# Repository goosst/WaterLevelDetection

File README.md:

# WaterLevelDetection

- [WaterLevelDetection](#waterleveldetection)
  * [Goal](#goal)
  * [Wishlist](#wishlist)
  * [Concept and used components](#concept-and-used-components)
    + [Controller](#controller)
    + [Pressure sensing and power electronics](#pressure-sensing-and-power-electronics)
  * [Implementation](#implementation)
    + [List of components](#list-of-components)
    + [Power electronics](#power-electronics)
    + [Current measurement](#current-measurement)
  * [Calibration](#calibration)
  * [Pictures](#pictures)
  * [Home assistant integration](#home-assistant-integration)
  * [(Possible) next steps](#-possible--next-steps)

## Goal

Measure the level of available water in a rainwater well and report in a home automation tool (here home assitant).

Spoiler alert: a 4-20mA, 24V converter using an ESP8266 was created for this.

## Wishlist

- Report level of water depth over WiFi (mqtt messages) 
- Since waterlevel only needs to be measured every x hours or days, use a deepsleep method to safe power and prevent heating / wear of components
- Use common components (through hole components for electronics, no SMD, ... )
- Be able to update software over the air

## Concept and used components

The measuring principle is based on water pressure, the pressure at the bottom of the well is proportional with the height of the water. Other methods using distance sensors sound quite unreliable (reflections, need to have a wide cone of free air to measure to the bottom of the well, ... ) or cumbersome (capacitive sensing).

### Controller
To take care of the Wifi and mqtt messages, an ESP8266 ([Wemos D1 mini](https://www.banggood.com/Geekcreit-D1-mini-V2_2_0-WIFI-Internet-Development-Board-Based-ESP8266-4MB-FLASH-ESP-12S-Chip-p-1143874.html?cur_warehouse=CN&rmmds=search&p=ET150713234951201708&custlinkid=1551683)) is used.

### Pressure sensing and power electronics
The sensor used here: [Pressure sensor](https://www.banggood.com/Submersible-Water-Level-Transmitter-Level-Transducer-Sensor-0-5mH2O-6m-Cable-p-1146896.html?rmmds=myorder&cur_warehouse=CN&p=ET150713234951201708&custlinkid=1551677).

This sensor creates an additional challenge, it returns a current between 4-20mA - proportional with the pressure - and requires a 24V supply voltage. 

- To measure the 4-20 mA, an INA219 sensor is used. This is a high side current sensor and additionally measures the bus voltage. This voltage will be used later to generate a reliable supply voltage.
- I was not able to identify a boost DC-DC converter that was through-hole (not SMD) and had an enable/disable pin. So I've decided to create a small dc-converter myself. It's important to use an N-channel mosfet which can be switched by a 3.3V signal from the ESP8266. All the rest (diode, inductor, capacitor) are quite standard components which you can find cheaply.
Other attempts made with breakoutboards using MT3608's, didn't really produce a stable output voltage when  component temperature got warmer etc.

## Implementation

Only the conceptual implementation is explained here, the source files contain the details.
<!--  -->

<!-- {{< figure src="concept.svg" title="PCB water level" height="200">}} -->

### List of components
| Components used      | 
| :------------- | 
|  [Wemos D1 mini](https://www.banggood.com/Geekcreit-D1-mini-V2_2_0-WIFI-Internet-Development-Board-Based-ESP8266-4MB-FLASH-ESP-12S-Chip-p-1143874.html?cur_warehouse=CN&rmmds=search&p=ET150713234951201708&custlinkid=1551683)| 
| [Pressure sensor](https://www.banggood.com/Submersible-Water-Level-Transmitter-Level-Transducer-Sensor-0-5mH2O-6m-Cable-p-1146896.html?rmmds=myorder&cur_warehouse=CN&p=ET150713234951201708&custlinkid=1551677) | 
| INA219: [example](https://nl.aliexpress.com/item/4000330275495.html?spm=a2g0s.9042311.0.0.28c74c4d10PHbJ) |
| N-channel mosfet switchable by 3.3V digital signal: example FQP30N06L |
| inductor, diode, capacitor, terminal |
| BMP280: to measure air pressure |

### Power electronics

- To reliably create the supply voltage for the pressure sensor (~24V), a feedback mechanism is used:
  - the INA219 sends the actual measured voltage over I2C to the wemos
  - in the Wemos a feedback loop (PI controller) adjusts the duty ratio of the mosfet, this guarantees a constant voltage over temperature etc. and doesn't require a consistent input supply voltage.
- Pin D8 of the WEMOS has to be used to generate the PWM signal for the dc-converter, when going to deepsleep this pin is inherently pulled down and the converter stops switching safely

A prototype pcb was created for it (with an additional - in the end unused - MAX417 current sensor), but the complexity is not very high to just solder it on a board ... .

### Current measurement
Typical breakout boards using the INA219, come with a 0.1 Ohm shunt resistor.
Only 4-20 mA is produced by the sensor, this means the voltage measured over the shunt would only be 0.4-2 mV which is basically noise ... .
According the datasheet, the range of the INA219 can be configured from 40 to 320mV, hence a resistor in the range of 2 to 15 Ohm would be acceptable. Here, a resistor of 10 Ohm is used.

<!--  -->

## Calibration

Now the hardware is setup, a calibration was done to correlate the measured shunt voltage / current with the pressure.
I've inserted the pressure sensor in water and came to this table:

| Level (meter)       | Shunt voltage mV     | shunt current mA     |
| :------------- | :----------: | -----------: |
|  0 (air) | 51   | 5.1    |
| 1   | 85 | 8.5 | 
| 1.5   | 99 | 9.9 | 

Luckily this leads to a linear trend :)

### Update May 2022

- Connected an additional cheap air pressure sensor BMP280 pressure sensor to the ESP (over i2c).
- moved further calculation of waterheight to a little python script triggered by home assistant

## Pictures

PCB board used (here with additional options for prototyping, the resistor of course gets replaced by the pressure sensor)
<!--  -->

Looks of the pressure sensor:
<!--  -->

Connections around the well are embedded in a two-component silicone gel:
<!--  -->

## Home assistant integration

a few mqtt topics were defined to read out and visualize the data:
```
  - platform: mqtt
    name: "Water level depth"
    state_topic: /sensor/WEMOSD1-14269530/data/waterdepth
    expire_after: 864000
    unit_of_measurement: "m"
    payload_available: "Online"
    payload_not_available: "water level sensor offline"
```

## (Possible) next steps

- optimize Kicad files (they work but there are additional items added for debugging purposes)
  - remove incorrect R_pulldown1 (or don't connect when using it)
  - remove place for redundant component (MAX 417 and related jumpers)
- create a proper 4-20mA, 24V converter using SMD components and compact converters

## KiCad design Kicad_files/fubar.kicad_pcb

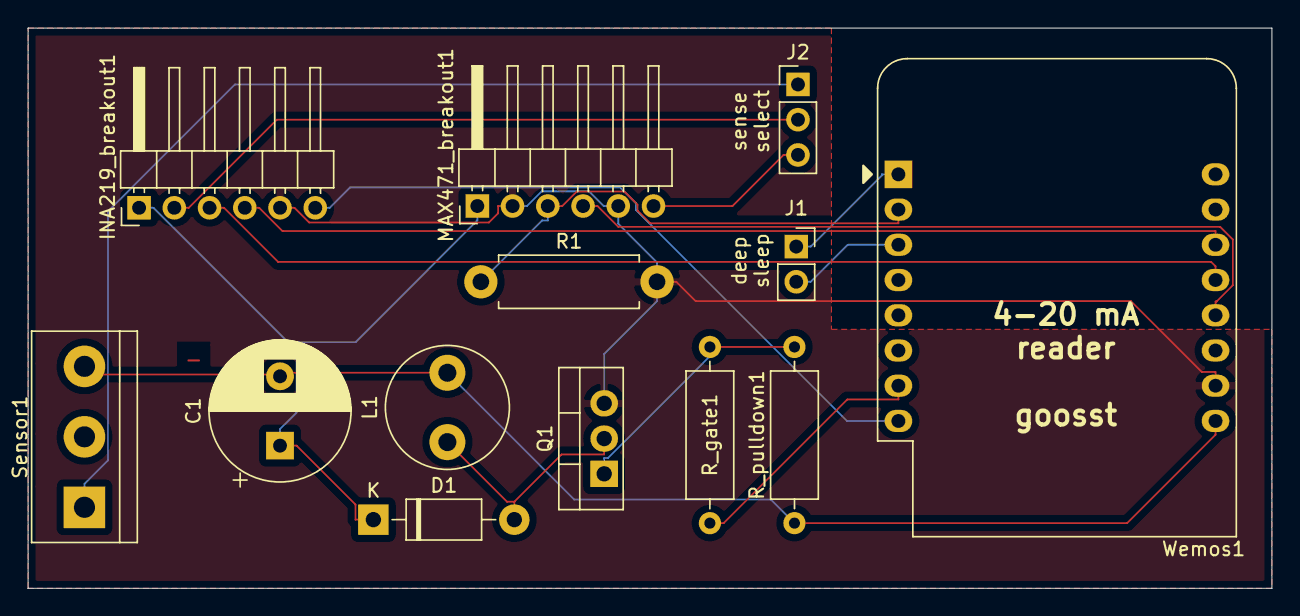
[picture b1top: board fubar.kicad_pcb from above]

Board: 2 copper layers, 89.7 x 40.4 mm, 13 parts (0 on the bottom side), 16 nets.

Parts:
C1: CP; CP_Radial_D10.0mm_P5.00mm
D1: 1N5817; D_DO-41_SOD81_P10.16mm_Horizontal
INA219_breakout1: Conn_01x06_Female; PinHeader_1x06_P2.54mm_Horizontal
J1: Conn_01x02_Female; PinSocket_1x02_P2.54mm_Vertical
J2: select_sensing; PinHeader_1x03_P2.54mm_Vertical
L1: L_Core_Ferrite; L_Radial_D8.7mm_P5.00mm_Fastron_07HCP
MAX471_breakout1: Conn_01x06_Female; PinHeader_1x06_P2.54mm_Horizontal
Q1: IRLZ44N; TO-220-3_Vertical
R1: 200k; R_Axial_DIN0411_L9.9mm_D3.6mm_P12.70mm_Horizontal
R_gate1: 200; R_Axial_DIN0309_L9.0mm_D3.2mm_P12.70mm_Horizontal
R_pulldown1: 10k; R_Axial_DIN0309_L9.0mm_D3.2mm_P12.70mm_Horizontal
Sensor1: Screw_Terminal_01x03; TerminalBlock_bornier-3_P5.08mm
Wemos1: WeMos_D1_mini; WEMOS_D1_mini_light

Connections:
+3V3: INA219_breakout1.6, Wemos1.8
+5V: C1.2, L1.2, R_pulldown1.1, Sensor1.3, Wemos1.9
/A0: MAX471_breakout1.3, R1.1, Wemos1.2
/D0: J1.2, Wemos1.3
/D3: MAX471_breakout1.4, Wemos1.12
/D8: R_gate1.2, Wemos1.7
/RST: J1.1, Wemos1.1
/SCL: INA219_breakout1.4, Wemos1.14
/SDA: INA219_breakout1.3, Wemos1.13
/Vdc_out_plus: C1.1, D1.1, INA219_breakout1.1, MAX471_breakout1.1
/Vshunt_INA219: INA219_breakout1.2, J2.2
/Vshunt_MAX417: J2.3, MAX471_breakout1.6
/Vshunt_select: J2.1, Sensor1.1
GNDREF: INA219_breakout1.5, MAX471_breakout1.2, MAX471_breakout1.5, Q1.3, R1.2, Wemos1.10
unnamed: D1.2, L1.1, Q1.2
unnamed: Q1.1, R_gate1.1, R_pulldown1.2

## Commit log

2021-05-08 initial documentation and ESP8266 files for waterlevel detection
2021-05-08 update documentation
2021-05-08 picture resizing fubar
2021-05-09 yet another figure resizing trial
2021-05-09 yet another figure resizing
2021-05-09 corrections documentation
2021-05-09 added TOC
2021-05-09 documentation update
2021-05-09 added kicad files prototype
2022-05-26 added BMP280 air pressure sensor
2022-05-26 merged missing items (basic waterdepth calculation)
2022-06-05 home assistant script to calculate waterdepth
